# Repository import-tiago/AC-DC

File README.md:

# AC-DC

AC-DC is a 240W linear bench power supply features two variable and independent 1.2V-24V and 5A outputs.

## Mounted Power Supply  

## Gerber Preview

## Schematic

### Contributing
0. Give this project a :star:
1. Create an issue and describe your idea.
2. [Fork it](https://github.com/import-tiago/AC-DC/fork).
3. Create your feature branch (`git checkout -b my-new-feature`).
4. Commit your changes (`git commit -a -m "Added feature title"`).
5. Publish the branch (`git push origin my-new-feature`).
6. Create a new pull request.
7. Done! :heavy_check_mark:

### License Information
<br /><span xmlns:dct="http://purl.org/dc/terms/" property="dct:title">AC-DC</span> by <a xmlns:cc="http://creativecommons.org/ns#" href="https://github.com/import-tiago" property="cc:attributionName" rel="cc:attributionURL">Tiago Silva</a> is licensed under a <a rel="license" href="http://creativecommons.org/licenses/by-sa/4.0/">Creative Commons Attribution-ShareAlike 4.0 International License</a>.<br />Permissions beyond the scope of this license may be available at <a xmlns:cc="http://creativecommons.org/ns#" href="https://twitter.com/import_tiago" rel="cc:morePermissions">tiagodepaulasilva@gmail.com</a>.

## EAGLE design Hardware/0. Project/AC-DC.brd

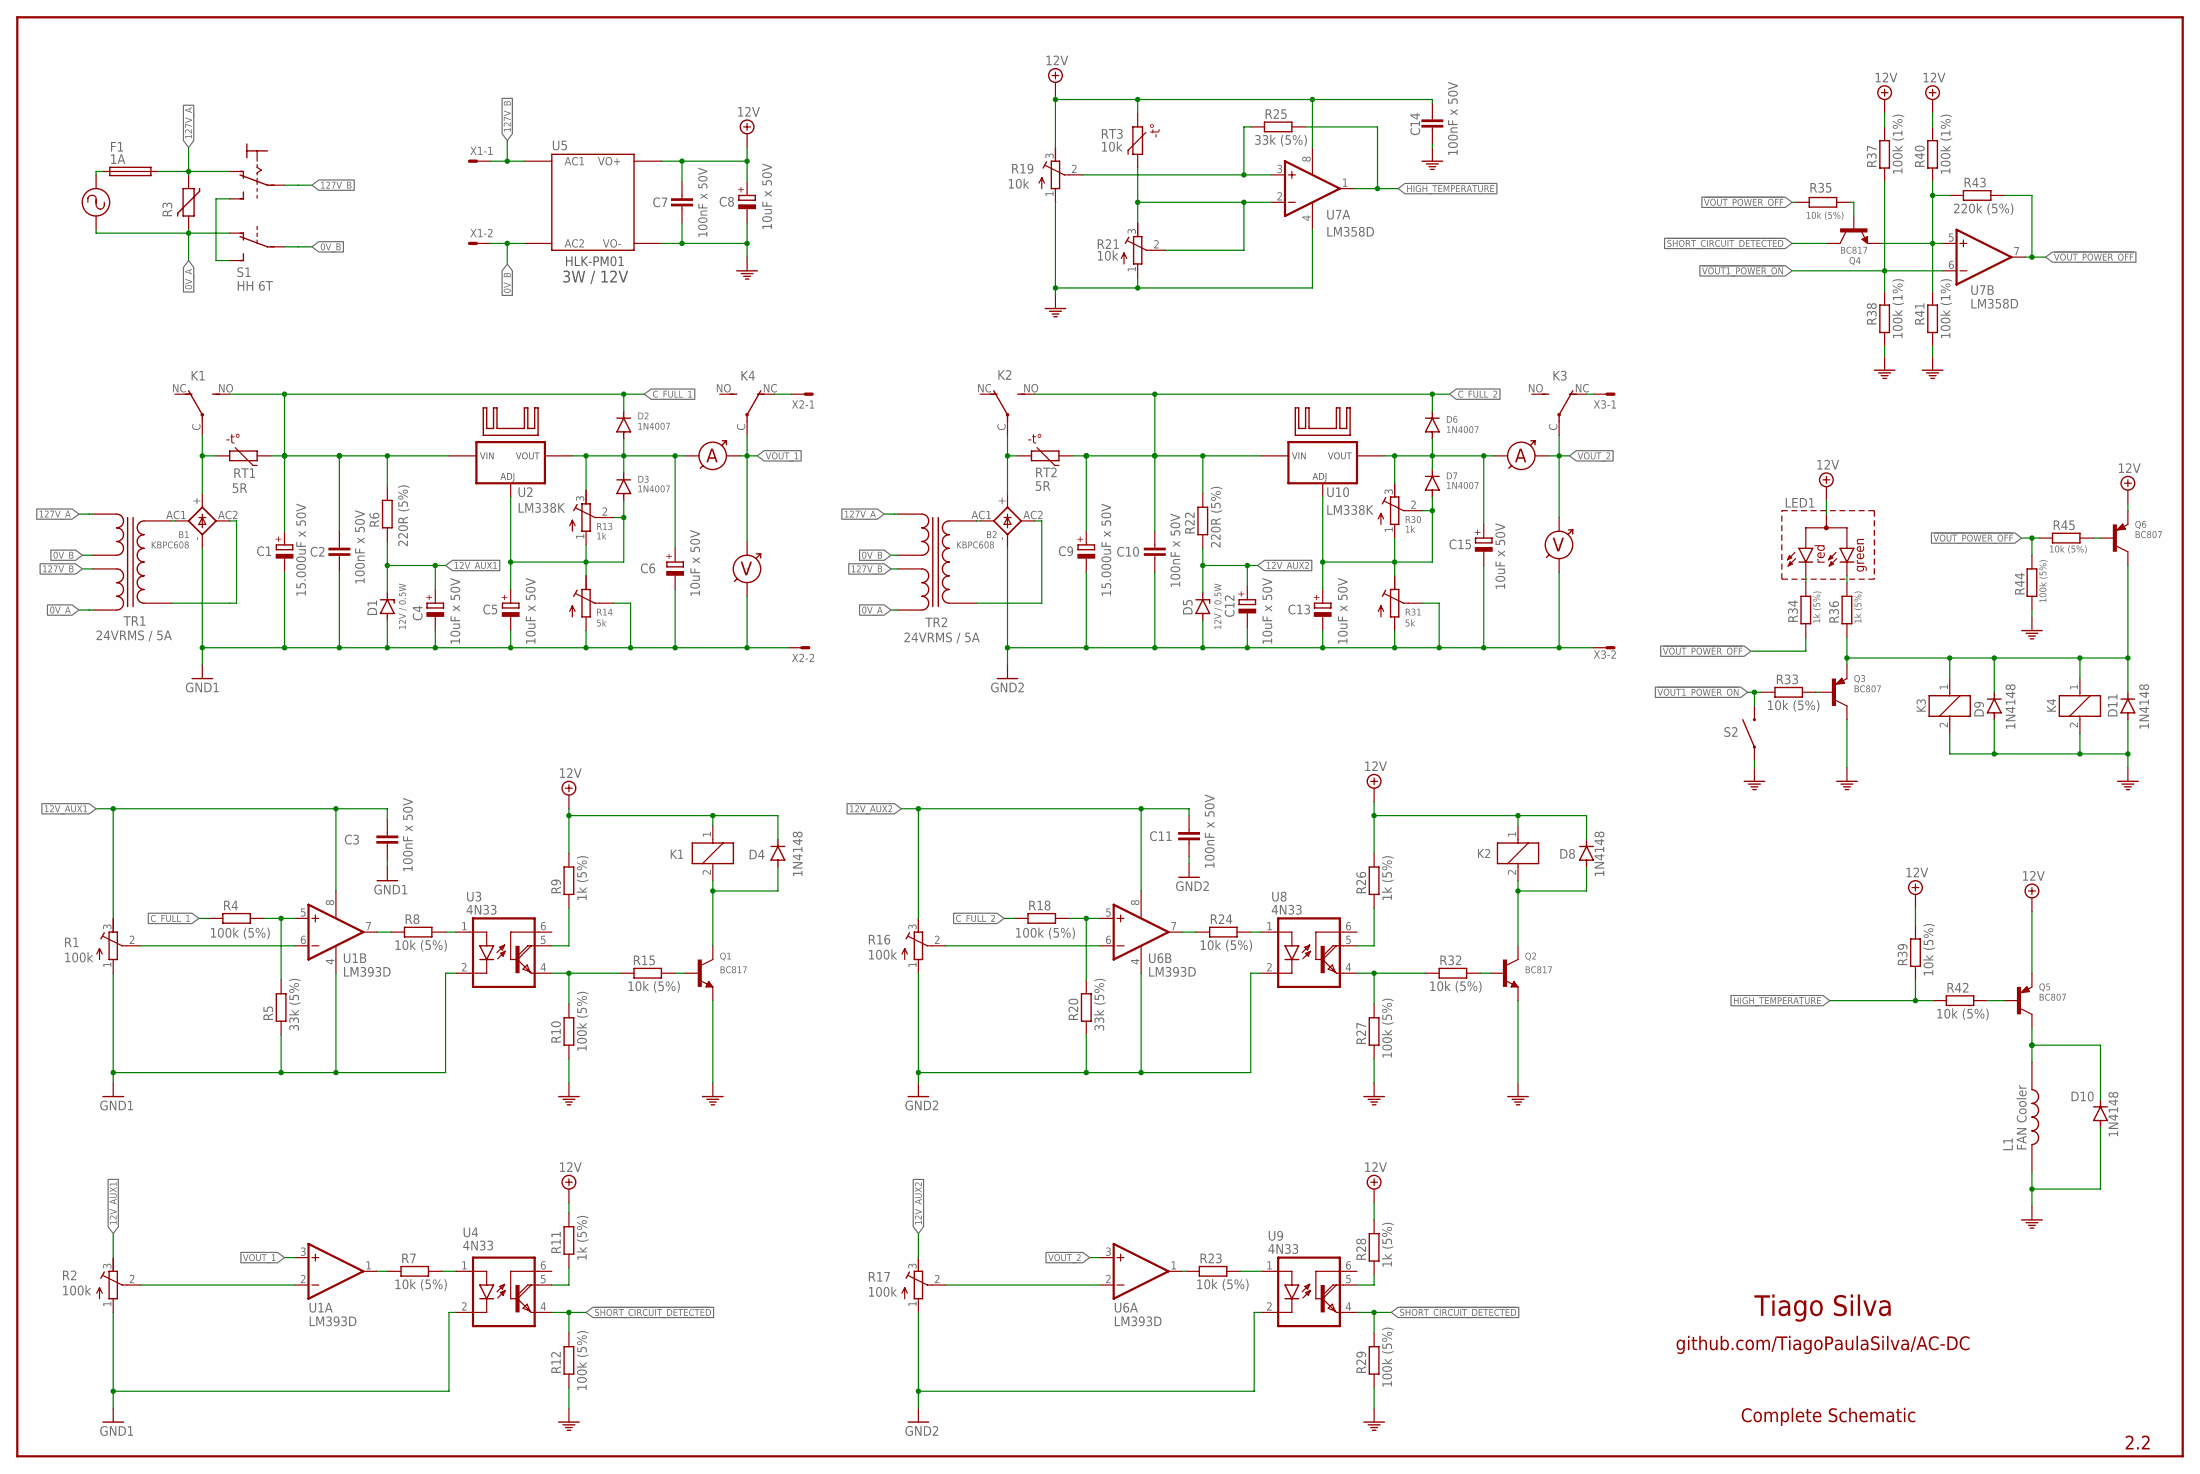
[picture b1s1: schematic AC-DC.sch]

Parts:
AMP1, AMP2: AMMETER
B1, B2: KBPC608; GBPC1
C1, C9: 15.000uF x 50V; EB35D
C2, C3, C7, C10, C11, C14: 100nF x 50V; C0805
C4, C5, C6, C8, C12, C13, C15: 10uF x 50V; 153CLV-0605
D1, D5: 12V / 0.5W; SOD80C
D2, D3, D6, D7: 1N4007; SOD-123_MINI-SMA
D4, D8, D9, D10, D11: 1N4148; SOD80C
K1, K2, K3, K4: CQ1-12V; CQ1
L1: FAN Cooler; MOLEX-2P
LED1: LED-BICOLOR-MOLEX3P; MOLEX3P
Q1, Q2, Q4: BC817; SOT23
Q3, Q5, Q6: BC807; SOT23-BEC
R1, R2, R16, R17: 100k; RTRIM3202
R4, R10, R12, R18, R27, R29, R44: 100k (5%); R0805
R5, R20, R25: 33k (5%); R0805
R6, R22: 220R (5%); R2512
R7, R8, R15, R23, R24, R32, R33, R35, R39, R42, R45: 10k (5%); R0805
R9, R11, R26, R28, R34, R36: 1k (5%); R0805
R13, R30: 1k; RTRIM3202
R14, R31: 5k; MOLEX3P
R19, R21: 10k; RTRIM3202
R37, R38, R40, R41: 100k (1%); R0805
R43: 220k (5%); R0805
RT1, RT2: 5R; 11MM
RT3: 10k; MOLEX2P
S2: SWITCH-MOLEX2P; MOLEX-2P
TR1, TR2: 24VRMS / 5A; 2PINS
U1, U6: LM393D; SO08
U2, U10: LM338K; MOLEX3P
U3, U4, U8, U9: 4N33; DIL6-SMD
U5: HLK-PM01
U7: LM358D; SO08
VOLT1, VOLT2: VOLTMETER
X1, X2, X3: 22-23-2021

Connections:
0V_B: U5.P$2 (AC2), X1.2
12V_AUX1: C3.1, C4.+, D1.C, R1.3 (E), R2.3 (E), R6.1, U1.8 (V+), VOLT1.P$1
12V_AUX2: C11.1, C12.+, D5.C, R16.3 (E), R17.3 (E), R22.1, U6.8 (V+), VOLT2.P$1
127V_B: U5.P$1 (AC1), X1.1
!SHORT_CIRCUIT_DETECTED!: Q4.3 (C), R12.2, R29.2, U4.4 (E), U9.4 (E)
!VOUT1_POWER_ON!: R33.2, R37.1, R38.2, S2.P$2 (2), U7.6 (-IN)
!VOUT1_POWER_ON!1: R11.1, U4.5 (COL)
!VOUT1_POWER_ON!2: R9.1, U3.5 (COL)
!VOUT1_POWER_ON!3: R28.1, U9.5 (COL)
!VOUT1_POWER_ON!4: R26.1, U8.5 (COL)
!VOUT_POWER_OFF!: R34.2, R35.1, R43.2, R44.1, R45.1, U7.7 (OUT)
+12V: C7.1, C8.+, C14.1, D4.C, D8.C, K1.1, K2.1, LED1.P$1 (A), Q5.E, Q6.E, R9.2, R11.2, R19.3 (E), R26.2, R28.2, R37.2, R39.2, R40.2, RT3.P$2 (2), U5.P$4 (VO+), U7.8 (V+)
C_FULL_1: C1.+, C2.1, D2.C, K1.NO (S), R4.2, R6.2, RT1.P$1 (1), U2.1 (VIN)
C_FULL_2: C9.+, C10.1, D6.C, K2.NO (S), R18.2, R22.2, RT2.P$1 (1), U10.1 (VIN)
GND1: B1.-, C1.-, C2.2, C3.2, C4.-, C5.-, C6.-, D1.A, R1.1 (A), R2.1 (A), R5.1, R14.P$1 (A), R14.P$3 (S), U1.4 (V-), U3.2 (C), U4.2 (C), VOLT1.P$2, X2.2
GND2: B2.-, C9.-, C10.2, C11.2, C12.-, C13.-, C15.-, D5.A, R16.1 (A), R17.1 (A), R20.1, R31.P$1 (A), R31.P$3 (S), U6.4 (V-), U8.2 (C), U9.2 (C), VOLT2.P$2, X3.2
HIGH_TEMPERATURE: R25.2, R39.1, R42.1, U7.1 (OUT)
unnamed: B1.+, K1.C, RT1.P$2 (2)
unnamed: D4.A, K1.2, Q1.3 (C)
unnamed: LED1.P$3 (CR), R34.1
unnamed: Q1.1 (B), R15.2
unnamed: R17.2 (S), U6.2 (-IN)
unnamed: R1.2 (S), U1.6 (-IN)
unnamed: Q6.B, R45.2
unnamed: B1.AC1, TR1.1
unnamed: B1.AC2, TR1.2
unnamed: D9.C, D11.C, K3.1, K4.1, Q3.E, Q6.C, R36.1
unnamed: LED1.P$2 (CG), R36.2
unnamed: Q3.B, R33.1
unnamed: AMP1.2, C6.+, D2.A, D3.C, R13.3 (E), U2.3 (VOUT)
unnamed: C5.+, D3.A, R13.1 (A), R13.2 (S), R14.P$2 (E), U2.2 (GND)
unnamed: K4.NC (O), X2.1
unnamed: R4.1, R5.2, U1.5 (+IN)
unnamed: R7.1, U1.1 (OUT)
unnamed: R7.2, U4.1 (A)
unnamed: Q4.2 (E), R40.1, R41.2, R43.1, U7.5 (+IN)
unnamed: Q4.1 (B), R35.2
unnamed: B2.AC1, TR2.1
unnamed: B2.AC2, TR2.2
unnamed: R2.2 (S), U1.2 (-IN)
unnamed: AMP2.2, C15.+, D6.A, D7.C, R30.3 (E), U10.3 (VOUT)
unnamed: C13.+, D7.A, R30.1 (A), R30.2 (S), R31.P$2 (E), U10.2 (GND)
unnamed: K3.NC (O), X3.1
unnamed: B2.+, K2.C, RT2.P$2 (2)
unnamed: Q5.B, R42.2
unnamed: D8.A, K2.2, Q2.3 (C)
unnamed: R21.2 (S), R21.3 (E), RT3.P$1 (1), U7.2 (-IN)
unnamed: R19.2 (S), R25.1, U7.3 (+IN)
unnamed: R8.1, U1.7 (OUT)
unnamed: D10.C, L1.P$1 (1), Q5.C
unnamed: R8.2, U3.1 (A)
unnamed: Q2.1 (B), R32.2
unnamed: R18.1, R20.2, U6.5 (+IN)
unnamed: R23.1, U6.1 (OUT)
unnamed: R16.2 (S), U6.6 (-IN)
unnamed: R23.2, U9.1 (A)
unnamed: R24.1, U6.7 (OUT)
unnamed: R24.2, U8.1 (A)
unnamed: R27.2, R32.1, U8.4 (E)
unnamed: R10.2, R15.1, U3.4 (E)
PE: C7.2, C8.-, C14.2, D9.A, D10.A, D11.A, K3.2, K4.2, L1.P$2 (2), Q1.2 (E), Q2.2 (E), Q3.C, R10.1, R12.1, R19.1 (A), R21.1 (A), R27.1, R29.1, R38.1, R41.1, R44.2, S2.P$1 (1), U5.P$3 (VO-), U7.4 (V-)
VOUT_1: AMP1.1, K4.C, U1.3 (+IN), VOLT1.P$3
VOUT_2: AMP2.1, K3.C, U6.3 (+IN), VOLT2.P$3

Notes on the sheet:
Tiago Silva
github.com/TiagoPaulaSilva/AC-DC
2.2
Complete Schematic
3W / 12V

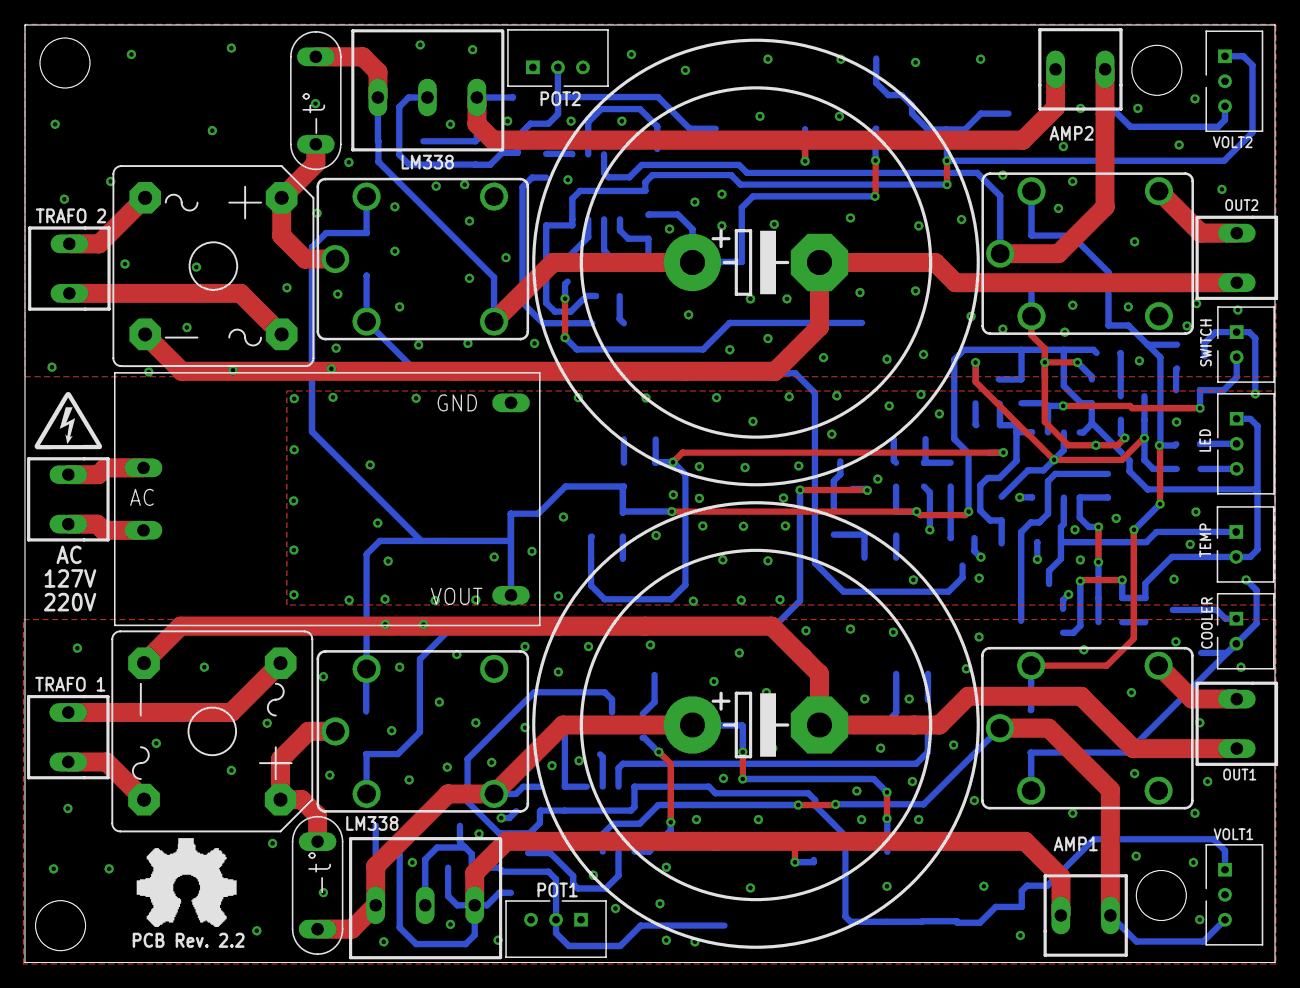
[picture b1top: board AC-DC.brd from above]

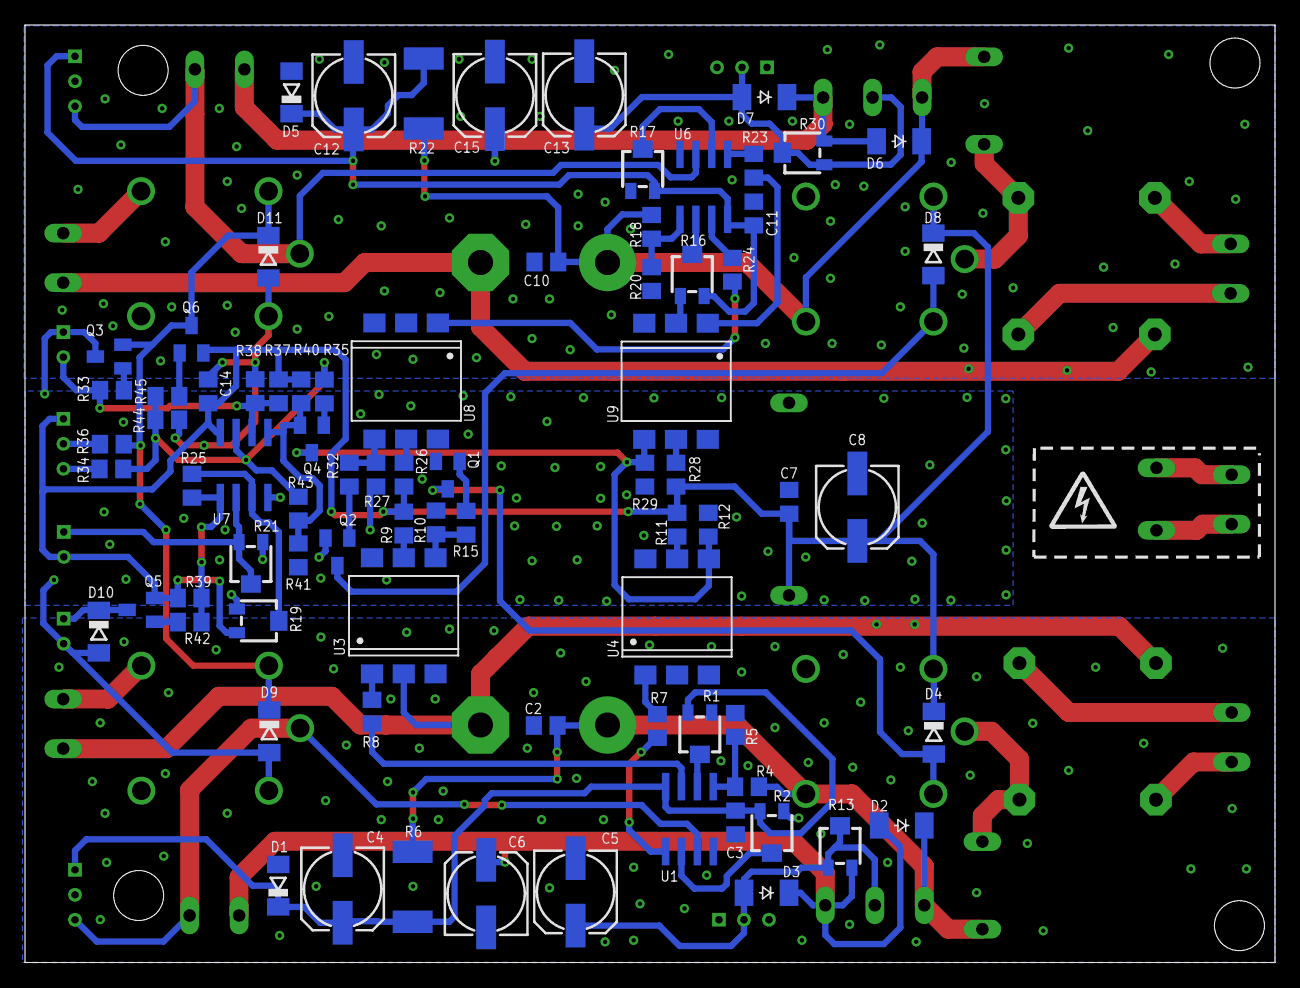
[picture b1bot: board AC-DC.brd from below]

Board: 2 copper layers, 100.0 x 75.0 mm, 107 parts (79 on the bottom side), 63 nets.

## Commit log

2019-08-01 .gitattributes added
2019-08-01 Schematic created
2019-08-02 Schematic design started
2019-08-02 New datasheets added
2019-08-02 Short-circuit added to schematic
2019-08-03 Schematic done
2019-08-04 Inrush current's capacitor circuit protect added
2019-08-04 Temperature Sensor for Heat Sink Added
2019-08-08 Minor improvements
2019-08-19 Schematic updated to 1.1 version
2019-08-20 PCB layout started
2019-08-21 PCB layout done
2019-08-21 Gerber files generated
2019-08-21 tStop added to high current traces
2019-08-21 Hidden components names/values of silkscreen
2019-08-21 GND high current return improved
2019-08-21 Components designators repositioned
2019-09-04 Set theme jekyll-theme-minimal
2019-11-16 Add images
2019-11-29 Schematic updated to 2.0
    - All Op. Amps. that was voltage compators was updated to LM393.
    - Fixed conflicts at +12V and +24V lines.
    - Now, there is only one temperature circuit monitor.
    - Ground from supply1 and supply2 is now isolated from each other
    (series and parallel association are now possible).
2019-12-04 Schematic 2.0 done
2019-12-04 Schematic image from 2.0 added
2019-12-04 Schematic 2.1 (better organization)
2019-12-16 Working on at 2.1 schematic
2019-12-16 Relay datasheet added
2020-01-15 Schematic and PCB layout 2.1 updated
2020-01-15 Gerber files from PCB 2.2
2020-01-15 Images used at PCB
2020-01-15 Gerber preview from 2.2 PCB layout
2020-01-15 PCB version ref added at PCB design
2020-01-15 File updated to 2.2 PCB rev.
2020-02-09 Images resized
2023-07-21 usernames in URLs updated
